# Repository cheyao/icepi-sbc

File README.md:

# Icepi SBC

A low-cost single-board computer for the H3 CPU: A cheap yet powerful Linux device that you can take anywhere.

| Interested? [Subscribe to updates!](https://cyao.dev/subscribe.html) | Check out [Icepi Zero](https://github.com/cheyao/icepi-zero) too |
| -------------------------------------------------------------------- | ---------------------------------------------------------------- |

If there's a lot of people interested, there's a chance that I'll try to sell this at a relatively low price :P

## Features

- H3 Quad-Core ARM Cortex-A7 @ 1.296GHz CPU
    - Mali400 MP2 OpenGL ES 2.0 GPU
- 512MiB of DDR3 RAM, stable at 696MHz (Upgradable to 1GiB)
- Ethernet PHY, WiFi & Bluetooth
- GPDI video out
- USB connectors:
    - 2x USB-A 
    - 2x USB-C (One OTG port)
    - 1x USB-C 100W PD power port
- 3.5mm audio jack
- uSD card slot
- eMMC 5.1 storage

## System support

The single-board computer is capable of running Linux (debian) and Android ([H3Droid](https://h3droid.com/project)). It can output 4k video via it's GPDI-A connector, output a tty consol via UART, or act as an remote host via ssh.

It's small, compact form factor allows it to be a nice portable computer that you can take anywhere! It supports GPU acceleration and 4k video decoding, letting you view anything in full confort.

## PCB

[Check out the online version here](https://github.com/cheyao/icepi-sbc/tree/main/hardware).

The PCB is only 4 layered, ensuring minimal cost and overhead during production. But for mass production 6 layers is recommended, putting solid ground on In.1 and In.4, then copy the power plane to In.2 and In.3. (Impedance matching might be required depending on stackup)

The current setup uses [JLCPCB's](https://jlcpcb.com/) JLC04161H-3313 stackup, and the BOM is optimized for use there. Using other fabs would require re-tuning the DDR3, USB and GPDI traces.

## Open source

This project is licensed under the [Solderpad](/LICENSE) hardware license, granting the maximum amount of liberty :)

It is also OSHWA certified under the identifier [FR000029](https://certification.oshwa.org/fr000029.html).

## Contact

Any questions? Dm `@Cyao.` on Discord (Send a friend request or join the KiCAD Discord server) or send an email to `cyao _at_ duck.com`!

## Bonus

POV: Running Android on the single board computer to study Eigenvectors in the middle of the night:

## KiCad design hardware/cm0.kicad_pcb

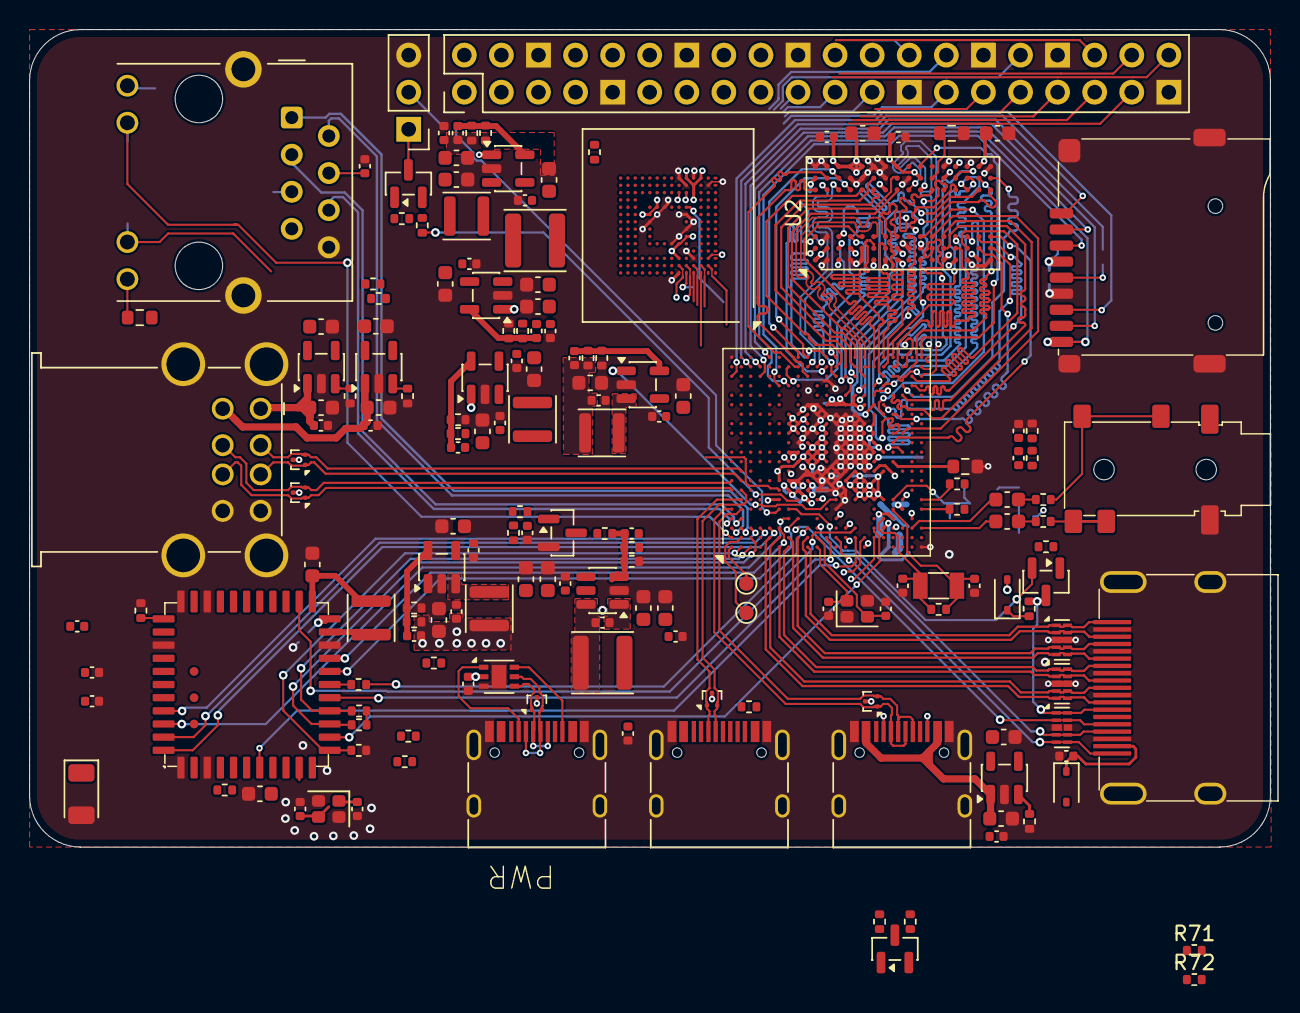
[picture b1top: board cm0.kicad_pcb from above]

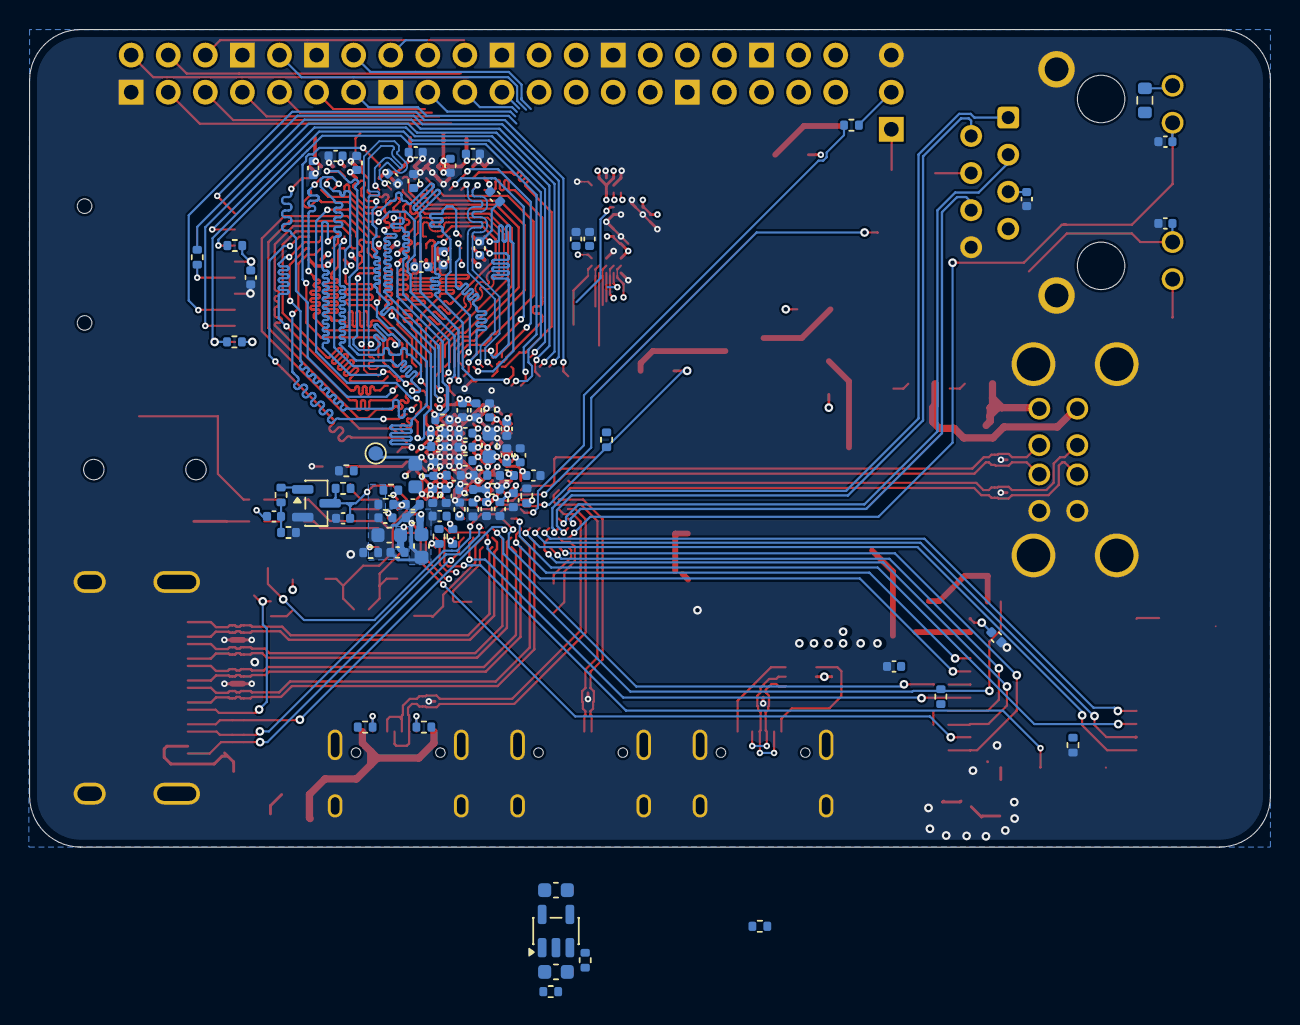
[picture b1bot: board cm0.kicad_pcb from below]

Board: 4 copper layers, 85.0 x 56.0 mm, 253 parts (85 on the bottom side), 209 nets.

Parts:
AE1: 2450AT18A100E; Johanson_2450AT18x100
C1, C2, C3, C4, C7, C8, C12, C14, C18, C19, C23, C24, C26, C27, C29, C31, C37, C38, C40, C41, C42, C43, C46, C47, C48, C49, C52, C53, C54, C55, C56, C57, C58, C60, C62, C65, C67, C70, C72, C76, C78, C81, C84, C85, C90, C92, C95, C98, C101, C104, C108, C110, C113, C114, C121, C122, C123, C124, C130: 100nF; C_0402_1005Metric
C5, C59, C75, C80, C82, C87, C93: 22uF; C_0603_1608Metric
C10, C11, C32, C129: 4.7uF; C_0402_1005Metric
C13, C16, C17, C21, C22, C25, C33, C35, C36, C45, C51, C107, C109, C111: 1uF; C_0402_1005Metric
C15, C20, C28, C30, C44, C50, C63, C64, C68, C69, C73, C79, C83, C86, C89, C96, C97, C99, C100, C102, C103, C105, C106, C112, C118, C125, C126: 10uF; C_0603_1608Metric
C34, C39, C127, C128: 15pF; C_0402_1005Metric
C61, C66, C71, C77, C88, C91: 22pF; C_0402_1005Metric
C94, C116, C117: NC; C_0402_1005Metric
C115, C119, C120: 10pF; C_0402_1005Metric
D1, D2: 1N5819WS; D_SOD-323
J1: USB_A_Stacked; USB_A_SHOUHAN_AF_SS-JB17.6_Horizontal_Stacked
J2, J3, J4: USB_C_Receptacle_USB2.0_14P; USB_C_Receptacle_HRO_TYPE-C-31-M-12
J5: GPDI_A; GPDI_A_XUNPU_001S
J6: Micro_SD_Card_Det1; microSD_TF-01A
J7: RJ45_Hanrun_HR913550A_Horizontal; RJ45_Hanrun_HR911105A_Horizontal
J8: Conn_01x03; PinHeader_1x03_P2.54mm_Vertical
J9: GPIO; PinHeader_2x20_P2.54mm_Vertical
J10: AudioJack_PJ-342; Jack_3.5mm_SHOUHAN_PJ-342
L1, L2, L3, L6, L7: 2.2uH; L_Sunlord_SWPA3015S
L4, L5: 2.2uH; L_Sunlord_SWPA4030S
Q1, Q3, Q4: BSN20; SOT-23
Q2: AO3415A; SOT-23
Q5: MMBT3904; SOT-23
R1: 6.04k; R_0402_1005Metric
R2, R9, R54, R55: 240; R_0603_1608Metric
R3, R5, R24: 0; R_0402_1005Metric
R4: 220k; R_0402_1005Metric
R6: 10M; R_0402_1005Metric
R7, R8, R39, R40, R71, R72: 2k; R_0402_1005Metric
R10, R11, R12, R15, R16, R20, R23, R25, R31, R32, R33, R36, R41, R45, R51, R56, R63, R64, R65: 10k; R_0402_1005Metric
R13, R17, R26: 2.2k; R_0402_1005Metric
R14: 15k; R_0402_1005Metric
R18, R19, R27, R52, R62, R69, R70: 100k; R_0402_1005Metric
R21: 11.8K; R_0402_1005Metric
R22, R28, R37, R38, R46, R47, R48, R49, R50: 33k; R_0402_1005Metric
R29, R30, R34, R35, R42, R43: 56k; R_0402_1005Metric
R44, R53, R57, R58, R59, R60: 33; R_0402_1005Metric
R61, R66, R67, R68: 47k; R_0402_1005Metric
TP1, TP2, TP3: TestPoint; TestPoint_Pad_D1.0mm
U1: H3; FBGA-347_14x14mm_Layout21x21_P0.65mm
U2: H5TQ4G63EFR; FBGA-96_7.5x13mm_Layout9x16_P0.8mm
U3, U4, U5, U8: SY8088; SOT-23-5
U6: SY8089A; SOT-23-5
U7: SY8113; TSOT-23-6
U9, U10, U11, U12: SY6280AAC; SOT-23-5
U13, U14, U15, U16, U18: TPD2EUSB30; Texas_DRT-3
U17: HUSB237; DFN-6-1EP_2x2mm_P0.65mm_EP1x1.6mm
U19, U20, U23: UCL0524P; Diodes_UDFN-10_1.0x2.5mm_P0.5mm
U21: EMMC5.1_BGA153; LFBGA-153_11.5x13mm_Layout14x14_P0.5mm
U22: AP6212
Y1: 32kHz; Crystal_SMD_3215-2Pin_3.2x1.5mm
Y2: 26MHz; Crystal_SMD_2016-4Pin_2.0x1.6mm
Y3: 24MHz; Crystal_SMD_2016-4Pin_2.0x1.6mm

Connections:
+1V1_CPUX: C15.1, C16.2, C17.2, C18.2, C19.2, C85.2, C86.1, C87.1, L5.2, U1.N8 (VDD-CPUX), U1.P6 (VDD-CPUX), U1.P7 (VDD-CPUX), U1.P8 (VDD-CPUX), U1.P9 (VDD-CPUX), U1.R6 (VDD-CPUX), U1.R7 (VDD-CPUX), U1.R8 (VDD-CPUX), U1.T6 (VDD-CPUX), U1.T7 (VDD-CPUX), U1.T8 (VDD-CPUX), U1.U6 (VDD-CPUX), U1.U9 (VDD-CPUX)
+1V2_SYSTEM: C4.2, C20.1, C21.2, C22.2, C23.2, C24.2, C77.1, C78.2, C79.1, C80.1, L4.2, R18.2, U1.F8 (EPHY_VDD), U1.H10 (VDD-SYS), U1.J10 (VDD-SYS), U1.J11 (VDD-SYS), U1.J12 (VDD-SYS), U1.K10 (VDD-SYS), U1.K11 (VDD-SYS), U1.K12 (VDD-SYS), U1.L10 (VDD-SYS), U1.L11 (VDD-SYS), U1.L12 (VDD-SYS), U1.L13 (VDD-SYS), U1.L14 (VDD-SYS)
+1V5: C35.2, C36.2, C37.2, C38.2, C42.1, C44.1, C45.2, C46.1, C47.1, C48.1, C49.1, C50.1, C51.2, C52.1, C53.1, C54.1, C55.1, C56.1, C57.1, C58.1, C66.1, C67.2, C68.1, L2.2, R7.2, R14.2, U1.L16 (VCC-DRAM), U1.M16 (VCC-DRAM), U1.N16 (VCC-DRAM), U1.P16 (VCC-DRAM), U1.P17 (VCC-DRAM), U1.R16 (VCC-DRAM), U1.T12 (VCC-DRAM), U1.T13 (VCC-DRAM), U1.T14 (VCC-DRAM), U1.T15 (VCC-DRAM), U1.U11 (VCC-DRAM), U2.A1 (VDDQ), U2.A8 (VDDQ), U2.B2 (VDD), U2.C1 (VDDQ), U2.C9 (VDDQ), U2.D2 (VDDQ), U2.D9 (VDD), U2.E9 (VDDQ), U2.F1 (VDDQ), U2.G7 (VDD), U2.H2 (VDDQ), U2.H9 (VDDQ), U2.K2 (VDD), U2.K8 (VDD), U2.N1 (VDD), U2.N9 (VDD), U2.R1 (VDD), U2.R9 (VDD)
+3V3: R41.1, U21.C6 (VCCQ), U21.E6 (VCC), U21.F5 (VCC), U21.J10 (VCC), U21.K9 (VCC), U21.M4 (VCCQ), U21.N4 (VCCQ), U21.P3 (VCCQ), U21.P5 (VCCQ)
+3V3_AVCC: C5.1, C7.2, C12.2, C27.2, C28.1, C29.2, C71.1, C72.2, C73.1, L3.2, Q2.2 (S), R10.1, R11.1, R15.2, R23.1, R61.1, R62.1, R65.1, R66.1, R68.1, U1.G9 (V33_TV), U1.K6 (VCC_RTC), U1.N3 (VCC_PLL), U1.V3 (AVCC)
+3V3_IO: C1.2, C2.2, C3.2, C8.2, C13.2, C14.2, C91.1, C92.2, C93.1, C109.2, C129.1, D1.2 (A), J6.4 (VDD), J9.1, L6.2, Q3.1 (G), Q4.1 (G), R25.2, R37.1, R42.1, R43.1, R54.1, R55.1, R56.1, R67.1, U1.G7 (EPHY_VCC), U1.G11 (VCC_USB), U1.G13 (VCC-IO), U1.G14 (VCC-IO), U1.G15 (VCC-IO), U1.H7 (VCC-PG), U1.H11 (VDD-EFUSEEBP), U1.H13 (VCC-IO), U1.H14 (VCC-IO), U1.J6 (GPDI_VCC), U1.J14 (VCC-IO), U1.J15 (VCC_PD)
+3V3_WIFI: C61.1, C62.2, C63.1, C112.1, C113.1, C114.1, L1.2, R12.2, R45.1, R46.1, R47.1, R48.1, R49.1, R50.1, R51.1, U22.9 (VBAT), U22.22 (VDDIO)
+5V: C59.1, C60.2, C64.1, C65.2, C69.1, C70.2, C75.1, C76.2, C82.1, C83.1, C84.2, C89.1, C90.2, C97.1, C100.1, C103.1, C106.1, C107.2, D2.2 (A), J4.A4 (VBUS), J4.A9 (VBUS), J4.B4 (VBUS), J4.B9 (VBUS), J9.2, J9.4, R39.2, R40.2, U3.1 (EN), U3.4 (IN), U4.4 (IN), U5.1 (EN), U5.4 (IN), U6.4 (IN), U7.5 (IN), U8.4 (IN), U9.4 (EN), U9.5 (IN), U10.4 (EN), U10.5 (IN), U11.4 (EN), U11.5 (IN), U12.4 (EN), U12.5 (IN), U17.2 (VBUS)
/Audio/AUDIO_L: C126.2, U1.AA3 (LINEOUTL)
/Audio/AUDIO_R: C125.2, U1.Y3 (LINEOUTR)
/Audio/TV_OUT: J10.1, U1.F10 (TVOUT)
/DDR3/A0: U1.T17 (SA0), U2.N3 (A0)
/DDR3/A1: U1.U18 (SA1), U2.P7 (A1)
/DDR3/A2: U1.V19 (SA2), U2.P3 (A2)
/DDR3/A3: U1.V20 (SA3), U2.N2 (A3)
/DDR3/A4: U1.V21 (SA4), U2.P8 (A4)
/DDR3/A5: U1.Y19 (SA5), U2.P2 (A5)
/DDR3/A6: U1.Y20 (SA6), U2.R8 (A6)
/DDR3/A7: U1.V15 (SA7), U2.R2 (A7)
/DDR3/A8: U1.W18 (SA8), U2.T8 (A8)
/DDR3/A9: U1.Y18 (SA9), U2.R3 (A9)
/DDR3/A10: U1.P19 (SA10), U2.L7 (A10/AP)
/DDR3/A11: U1.N19 (SA11), U2.R7 (A11)
/DDR3/A12: U1.R18 (SA12), U2.N7 (A12/~BC)
/DDR3/A13: U1.V12 (SA13), U2.T3 (A13)
/DDR3/A14: U1.N17 (SA14), U2.T7 (A14)
/DDR3/A15: U1.R17 (SA15), U2.M7 (A15)
/DDR3/BA0: U1.W17 (SBA0), U2.M2 (BA0)
/DDR3/BA1: U1.T18 (SBA1), U2.N8 (BA1)
/DDR3/BA2: U1.V17 (SBA2), U2.M3 (BA2)
/DDR3/CKE: U1.AA21 (SCKE0), U2.K9 (CKE)
/DDR3/CLK+: U1.AA19 (SCK), U2.J7 (CK)
/DDR3/CLK-: U1.AA20 (SCKB), U2.K7 (~CK)
/DDR3/DQ0: U1.T20 (SDQ5), U2.E3 (DQ0)
/DDR3/DQ1: U1.P20 (SDQ2), U2.F7 (DQ1)
/DDR3/DQ2: U1.U19 (SDQ6), U2.F2 (DQ2)
/DDR3/DQ3: U1.N20 (SDQ0), U2.F8 (DQ3)
/DDR3/DQ4: U1.U20 (SDQ7), U2.H3 (DQ4)
/DDR3/DQ5: U1.P21 (SDQ1), U2.H8 (DQ5)
/DDR3/DQ6: U1.U21 (SDQ3), U2.G2 (DQ6)
/DDR3/DQ7: U1.R19 (SDQ4), U2.H7 (DQ7)
/DDR3/DQ8: U1.J21 (SDQ11), U2.D7 (DQ8)
/DDR3/DQ9: U1.M21 (SDQ14), U2.C3 (DQ9)
/DDR3/DQ10: U1.H21 (SDQ10), U2.C8 (DQ10)
/DDR3/DQ11: U1.M19 (SDQ15), U2.C2 (DQ11)
/DDR3/DQ12: U1.J19 (SDQ8), U2.A7 (DQ12)
/DDR3/DQ13: U1.L21 (SDQ13), U2.A2 (DQ13)
/DDR3/DQ14: U1.H20 (SDQ9), U2.B8 (DQ14)
/DDR3/DQ15: U1.L20 (SDQ12), U2.A3 (DQ15)
/DDR3/DQM0: U1.M20 (SDQM0), U2.E7 (LDM)
/DDR3/DQM1: U1.G20 (SDQM1), U2.D3 (UDM)
/DDR3/DQS0+: U1.R20 (SDQS0), U2.F3 (LDQS)
/DDR3/DQS0-: U1.R21 (SDQS0B), U2.G3 (~LDQS)
/DDR3/DQS1+: U1.K20 (SDQS1), U2.C7 (UDQS)
/DDR3/DQS1-: U1.J20 (SDQS1B), U2.B7 (~UDQS)
/DDR3/ODT: U1.W11 (SODT0), U2.K1 (ODT)
/DDR3/~CAS: U1.U15 (SCAS), U2.K3 (~CAS)
/DDR3/~CS: U1.W20 (SCS0), U2.L2 (~CS)
/DDR3/~RAS: U1.V13 (SRAS), U2.J3 (~RAS)
/DDR3/~RESET: U1.U16 (SRST), U2.T2 (~RESET)
/DDR3/~WE: U1.W13 (SWE), U2.L3 (~WE)
/GPDI/GPDI_CEC: Q3.2 (S), R37.2, U1.G5 (GPDI_CEC)
/GPDI/GPDI_CECI: J5.13 (CEC), Q3.3 (D), R38.2, U23.1, U23.10
/GPDI/GPDI_CLK+: J5.10 (CK+), U1.F2 (GPDI_CLK+), U20.4, U20.7
/GPDI/GPDI_CLK-: J5.12 (CK-), U1.E2 (GPDI_CLK-), U20.5, U20.6
/GPDI/GPDI_D0+: J5.7 (D0+), U1.G1 (GPDI_D0+), U20.1, U20.10
/GPDI/GPDI_D0-: J5.9 (D0-), U1.F1 (GPDI_D0-), U20.2, U20.9
/GPDI/GPDI_D1+: J5.4 (D1+), U1.H2 (GPDI_D1+), U19.4, U19.7
/GPDI/GPDI_D1-: J5.6 (D1-), U1.G2 (GPDI_D1-), U19.5, U19.6
/GPDI/GPDI_D2+: J5.1 (D2+), U1.J1 (GPDI_D2+), U19.1, U19.10
/GPDI/GPDI_D2-: J5.3 (D2-), U1.J2 (GPDI_D2-), U19.2, U19.9
/GPDI/GPDI_HPD: J5.19 (HPD), U1.M2 (GPDI_HPD), U23.5, U23.6
/GPDI/GPDI_SCL: J5.15 (SCL), R40.1, U1.H3 (GPDI_SCL), U23.2, U23.9
/GPDI/GPDI_SDA: J5.16 (SDA), R39.1, U1.K3 (GPDI_SDA), U23.4, U23.7
/GPIO/CPU_RX: R57.1, U1.H6 (PA5)
/GPIO/CPU_TX: R58.1, U1.F5 (PA4)
/H3/AGND: C28.2, C29.1, C30.2, C31.1, C32.2, C33.1, R4.2, R5.1, U1.U3 (AGND)
/H3/BT_HOST_WAKE: U1.P2 (PL2), U22.7 (BT_HOST_WAKE)
/H3/BT_RXD: U1.D3 (UART1_RX), U22.43 (UART_RXD)
/H3/BT_TXD: U1.G4 (UART1_TX), U22.42 (UART_TXD)
/H3/BT_WAKE: R45.2, R69.1, U1.A13 (PA20), U22.6 (BT_WAKE)
/H3/EPHY_LINK_LED: C124.1, J7.10, U1.A2 (EPHY_LINK_LED)
/H3/EPHY_RX+: J7.3 (RD+), U1.B4 (EPHY_RXP)
/H3/EPHY_RX-: J7.6 (RD-), U1.A4 (EPHY_RXN)
/H3/EPHY_SPD_LED: C123.1, J7.11, U1.F7 (EPHY_SPD_LED)
/H3/EPHY_TX+: J7.1 (TD+), U1.B3 (EPHY_TXP)
/H3/EPHY_TX-: J7.2 (TD-), U1.A3 (EPHY_TXN)
/H3/KEYADC: R62.2, U1.AA5 (KEYADC)
/H3/PWR_CPUFB: C88.1, R20.1, TP1.1, U1.T10 (VDD-CPUFB)
/H3/PWR_DRAM: R10.2, U1.M6 (PL9), U4.1 (EN)
/H3/PWR_IO: Q2.1 (G), R27.2, U1.R2 (PL5)
/H3/PWR_KEY: R66.2, U1.R1 (PL3)
/H3/PWR_SYSTEM: R11.2, U1.T2 (PL8), U6.1 (EN), U7.4 (EN)
/H3/PWR_VSET: R24.2, U1.T4 (PL6)
/H3/RECOVERY: R68.2, U1.N2 (PL4)
/H3/RESET: C130.2, Q5.3 (C), R65.2, U1.V6 (RESET)
/H3/SDIO_CLK: R53.1, U1.J3 (SDC1_CLK)
/H3/SDIO_CMD: R50.2, U1.L2 (SDC1_CMD), U22.16 (SDIO_DATA_CMD)
/H3/SDIO_D0: R49.2, U1.H4 (SDC1_D0), U22.18 (SDIO_DATA_0)
/H3/SDIO_D1: R48.2, U1.F3 (SDC1_D1), U22.19 (SDIO_DATA_1)
/H3/SDIO_D2: R47.2, U1.C2 (SDC1_D2), U22.14 (SDIO_DATA_2)
/H3/SDIO_D3: R46.2, U1.C1 (SDC1_D3), U22.15 (SDIO_DATA_3)
/H3/SD_CLK: R44.1, U1.D20 (PF2)
/H3/SD_CMD: J6.3 (CMD), R42.2, U1.F18 (PF3)
/H3/SD_D0: J6.7 (DAT0), U1.A19 (PF1)
/H3/SD_D1: J6.8 (DAT1), U1.D19 (PF0)
/H3/SD_D2: J6.1 (DAT2), U1.C20 (PF5)
/H3/SD_D3: J6.2 (DAT3/CD), U1.E21 (PF4)
/H3/SD_DET: J6.9 (DET), R43.2, U1.G18 (PF6)
/H3/UBOOT: R67.2, U1.W6 (UBOOT)
/H3/USB_D0+: J2.A7 (D-), J2.B7 (D-), U1.A5 (USB_D0+), U13.1 (D+)
/H3/USB_D0-: J2.A6 (D+), J2.B6 (D+), U1.B5 (USB_D0-), U13.2 (D-)
/H3/USB_D1+: J3.A7 (D-), J3.B7 (D-), U1.B6 (USB_D1+), U15.1 (D+)
/H3/USB_D1-: J3.A6 (D+), J3.B6 (D+), U1.B7 (USB_D1-), U15.2 (D-)
/H3/USB_D2+: J1.7 (D2+), U1.A7 (USB_D2+), U14.1 (D+)
/H3/USB_D2-: J1.6 (D2-), U1.A8 (USB_D2-), U14.2 (D-)
/H3/USB_D3+: J1.3 (D1+), U1.B8 (USB_D3+), U16.1 (D+)
/H3/USB_D3-: J1.2 (D1-), U1.B9 (USB_D3-), U16.2 (D-)
/H3/VRA1: C33.2, U1.Y4 (VRA1)
/H3/VRA2: C32.1, R4.1, U1.W5 (VRA2)
/H3/VRP: C30.1, C31.2, U1.V4 (VRP)
/H3/WIFI_32K: R51.2, U1.P3 (X32KFOUT), U22.24 (LPO)
/H3/WL_HOST_WAKE: U1.T3 (PL7), U22.13 (WL_HOST_WAKE)
/H3/WL_REG_ON: R52.1, U1.B1 (PG13), U22.12 (WL_REG_ON)
/H3/X24MI: C127.1, U1.K2 (X24MIN), Y3.2
/H3/X24MO: C128.1, U1.K1 (X24MOUT), Y3.4
/H3/X32KI: C34.1, R6.1, U1.V5 (X32KIN), Y1.2
/H3/X32KO: C39.1, R6.2, U1.U4 (X32KOUT), Y1.1
/H3/eMMC_CLK: U1.A17 (PC5), U21.M6 (CLK)
/H3/eMMC_CMD: R41.2, U1.E16 (PC6), U21.M5 (CMD)
/H3/eMMC_D0: U1.B18 (PC8), U21.A3 (DAT0)
/H3/eMMC_D1: U1.C17 (PC9), U21.A4 (DAT1)
/H3/eMMC_D2: U1.D17 (PC10), U21.A5 (DAT2)
/H3/eMMC_D3: U1.C18 (PC11), U21.B2 (DAT3)
/H3/eMMC_D4: U1.B17 (PC12), U21.B3 (DAT4)
/H3/eMMC_D5: U1.B19 (PC13), U21.B4 (DAT5)
/H3/eMMC_D6: U1.F17 (PC14), U21.B5 (DAT6)
/H3/eMMC_D7: U1.C19 (PC15), U21.B6 (DAT7)
/H3/~BT_CTS: U1.E3 (UART1_CTS), U22.44 (UART_CTS_N)
/H3/~BT_RST: R70.1, U1.D13 (PA9), U22.34 (BT_RST_N)
/H3/~BT_RTS: U1.C3 (UART1_RTS), U22.41 (UART_RTS_N)
/H3/~eMMC_RST: U1.H16 (PC16), U21.K5 (~RST)
/USB/PWR_CC1: J4.A5 (CC1), U17.1 (CC1)
/USB/PWR_CC2: J4.B5 (CC2), U17.6 (CC2)
/USB/PWR_D+: J4.A6 (D+), J4.B6 (D+), U17.4 (D+), U18.1 (D+)
/USB/PWR_D-: J4.A7 (D-), J4.B7 (D-), U17.5 (D-), U18.2 (D-)
/USB/USB_VBUS0: C95.2, C96.1, J2.A4 (VBUS), J2.A9 (VBUS), J2.B4 (VBUS), J2.B9 (VBUS), R29.1, R30.1, U9.1 (OUT)
/USB/USB_VBUS1: C104.2, C105.1, J3.A4 (VBUS), J3.A9 (VBUS), J3.B4 (VBUS), J3.B9 (VBUS), R34.1, R35.1, U12.1 (OUT)
/USB/USB_VBUS2: C98.2, C99.1, J1.1 (VBUS1), U10.1 (OUT)
/USB/USB_VBUS3: C101.2, C102.1, J1.5 (VBUS2), U11.1 (OUT)
GND: AE1.2 (Shield), C1.1, C2.1, C3.1, C4.1, C5.2, C7.1, C8.1, C10.2, C11.2, C12.1, C13.1, C14.1, C15.2, C16.1, C17.1, C18.1, C19.1, C20.2, C21.1, C22.1, C23.1, C24.1, C25.1, C26.1, C27.1, C34.2, C35.1, C36.1, C37.1, C38.1, C39.2, C40.2, C41.2, C43.2, C44.2, C45.1, C46.2, C47.2, C48.2, C49.2, C50.2, C51.1, C52.2, C53.2, C54.2, C55.2, C56.2, C57.2, C58.2, C59.2, C60.1, C62.1, C63.2, C64.2, C65.1, C67.1, C68.2, C69.2, C70.1, C72.1, C73.2, C75.2, C76.1, C78.1, C79.2, C80.2, C82.2, C83.2, C84.1, C85.1, C86.2, C87.2, C89.2, C90.1, C92.1, C93.2, C94.2, C95.1, C96.2, C97.2, C98.1, C99.2, C100.2, C101.1, C102.2, C103.2, C104.1, C105.2, C106.2, C107.1, C108.1, C109.1, C110.2, C111.1, C112.2, C113.2, C114.2, C116.2, C117.2, C118.2, C119.2, C120.2, C121.1, C122.1, C123.2, C124.2, C127.2, C128.2, C130.1, J1.4 (GND1), J1.8 (GND2), J1.9 (Shield), J2.A1 (GND), J2.A12 (GND), J2.B1 (GND), J2.B12 (GND), J2.S1 (SHIELD), J3.A1 (GND), J3.A12 (GND), J3.B1 (GND), J3.B12 (GND), J3.S1 (SHIELD), J4.A1 (GND), J4.A12 (GND), J4.B1 (GND), J4.B12 (GND), J4.S1 (SHIELD), J5.2 (D2S), J5.5 (D1S), J5.8 (D0S), J5.11 (CKS), J5.17 (GND), J5.SH, J6.6 (VSS), J6.10 (SHIELD), J7.8, J7.SH, J8.3, J9.6, J9.9, J9.14, J9.20, J9.25, J9.30, J9.34, J9.39, J10.2, Q1.2 (S), Q5.2 (E), R1.2, R2.1, R3.2, R5.2, R8.1, R9.2, R13.1, R16.1, R17.1, R19.1, R21.2, R26.1, R27.1, R28.2, R31.2, R32.2, R33.2, R36.2, R52.2, R63.2, R69.2, R70.2, U1.A21 (GND), U1.AA1 (GND), U1.G8 (GND), U1.H8 (GND_TV), U1.H12 (GND), U1.H15 (GND), U1.J9 (GND), U1.J13 (GND), U1.J16 (GND), U1.K7 (GND), U1.K8 (GND), U1.K9 (GND), U1.K13 (GND), U1.K14 (GND), U1.K15 (GND), U1.K16 (GND), U1.L8 (GND), U1.L9 (GND), U1.L15 (GND), U1.M5 (GPDI_GND), U1.M7 (GND), U1.M8 (GND), U1.M9 (GND), U1.M10 (GND), U1.M11 (GND), U1.M12 (GND), U1.M13 (GND), U1.M14 (GND), U1.M15 (GND), U1.N7 (GND), U1.N9 (GND), U1.N10 (GND), U1.N11 (GND), U1.N12 (GND), U1.N13 (GND), U1.N14 (GND), U1.N15 (GND), U1.P10 (GND), U1.P11 (GND), U1.P12 (GND), U1.P13 (GND), U1.P14 (GND), U1.P15 (GND), U1.R9 (GND), U1.R10 (GND), U1.R11 (GND), U1.R12 (GND), U1.R13 (GND), U1.R14 (GND), U1.T11 (GND), U2.A9 (VSS), U2.B1 (VSSQ), U2.B3 (VSS), U2.B9 (VSSQ), U2.D1 (VSSQ), U2.D8 (VSSQ), U2.E1 (VSS), U2.E2 (VSSQ), U2.E8 (VSSQ), U2.F9 (VSSQ), U2.G1 (VSSQ), U2.G8 (VSS), U2.G9 (VSSQ), U2.J2 (VSS), U2.J8 (VSS), U2.M1 (VSS), U2.M9 (VSS), U2.P1 (VSS), U2.P9 (VSS), U2.T1 (VSS), U2.T9 (VSS), U3.2 (GND), U4.2 (GND), U5.2 (GND), U6.2 (GND), U7.2 (GND), U8.2 (GND), U9.2 (GND), U10.2 (GND), U11.2 (GND), U12.2 (GND), U13.3 (GND), U14.3 (GND), U15.3 (GND), U16.3 (GND), U17.3 (VSET), U17.7 (GND), U18.3 (GND), U19.3, U19.8, U20.3, U20.8, U21.A6 (VSS), U21.C4 (VSSQ), U21.E7 (VSS), U21.G5 (VSS), U21.H10 (VSS), U21.J5 (VSS), U21.K8 (VSSQ), U21.N2 (VSSQ), U21.N5 (VSSQ), U21.P4 (VSSQ), U21.P6 (VSSQ), U22.1 (GND), U22.3 (GND), U22.20 (GND), U22.31 (GND), U22.33 (GND), U22.36 (GND), U23.3, U23.8, Y2.2, Y2.4, Y3.1, Y3.3
unnamed: AE1.1 (A), C115.2, C116.1, C117.1
unnamed: C125.1, R59.2
unnamed: C126.1, R60.2
unnamed: C129.2, R63.1, R64.1
unnamed: D1.1 (K), R38.1
unnamed: C108.2, D2.1 (K), J5.18 (+5V)
unnamed: J2.A5 (CC1), R29.2
unnamed: J2.B5 (CC2), R30.2
unnamed: J3.A5 (CC1), R34.2
unnamed: J3.B5 (CC2), R35.2
unnamed: J6.5 (CLK), R44.2
unnamed: J7.9, R55.2
unnamed: J7.12, R54.2
unnamed: C122.2, J7.5 (RCT)
unnamed: C121.2, J7.4 (TCT)
unnamed: J8.1, Q4.3 (D)
unnamed: J8.2, R58.2
unnamed: J10.3, J10.5, R59.1
unnamed: J10.4, J10.6, R60.1
unnamed: Q1.3 (D), R22.2
unnamed: C94.1, Q1.1 (G), R23.2, R24.1
unnamed: Q2.3 (D), R28.1, U8.1 (EN)
unnamed: Q4.2 (S), R56.2, R57.2
unnamed: Q5.1 (B), R64.2
unnamed: R2.2, U1.V10 (SZQ)
unnamed: C10.1, U1.G10 (VDD-EFUSE)
unnamed: R1.1, U1.F6 (EPHY_RTX)
unnamed: R3.1, U1.T9 (GND-CPUFB)
unnamed: TP2.1, U1.A1 (JTAG-SEL0)
unnamed: TP3.1, U1.B2 (JTAG-SEL1)
unnamed: R61.2, U1.AA6 (NMI)
unnamed: R9.1, U2.L8 (ZQ)
unnamed: C61.2, R12.1, R13.2, U3.5 (FB)
unnamed: L1.1, U3.3 (LX)
unnamed: C66.2, R14.1, R16.2, U4.5 (FB)
unnamed: L2.1, U4.3 (LX)
unnamed: C71.2, R15.1, R17.2, U5.5 (FB)
unnamed: L3.1, U5.3 (LX)
unnamed: C77.2, R18.1, R19.2, U6.5 (FB)
unnamed: L4.1, U6.3 (LX)
unnamed: C81.2, U7.1 (BS)
unnamed: C88.2, R20.2, R21.1, R22.1, U7.3 (FB)
unnamed: C81.1, L5.1, U7.6 (LX)
unnamed: C91.2, R25.1, R26.2, U8.5 (FB)
unnamed: L6.1, U8.3 (LX)
unnamed: R31.1, U9.3 (ISET)
unnamed: R32.1, U10.3 (ISET)
unnamed: R33.1, U11.3 (ISET)
unnamed: R36.1, U12.3 (ISET)
unnamed: C110.1, C111.2, U21.C2 (VDDI)
unnamed: R53.2, U22.17 (SDIO_DATA_CLK)
unnamed: C118.1, L7.2, U22.23 (VIN_LDO)
unnamed: L7.1, U22.21 (VIN_LDO_OUT)
unnamed: C115.1, U22.2 (WL_BT_ANT)
unnamed: C120.1, U22.10 (XTAL_IN), Y2.3
unnamed: C119.1, U22.11 (XTAL_OUT), Y2.1
VDD_CPUS: C11.1, C25.2, C26.2, U1.J7 (VDD-CPUS), U1.J8 (VDD-CPUS), U1.M4 (RTC_VIO)
VREF: C40.1, C41.1, C42.2, C43.1, R7.1, R8.2, U1.T16 (SVREF), U2.H1 (VREFDQ), U2.M8 (VREFCA)

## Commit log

2025-10-31 Routed DDR3
2025-11-02 Drew wifi, GPDI, and re-routed DDR3
2025-11-05 Added TVS diodes, RF switch and changed RJ45 conn
2025-11-09 Drew most of DC DC converters
2025-11-12 Laid out the DCDC bucks
2025-11-13 Even more routing
2025-11-14 Less than 100 traces left
2025-11-15 Add some vital info!
2025-11-18 Improve routing and add test pads
2025-11-19 Production ready
2025-11-24 Improve heat dissipation and layout
2025-12-05 Add some more decoupling and move trace
2025-12-07 Add link
2025-12-24 Bonus pic :-P
2025-12-28 Fix typo in README for Android section
2026-01-09 Pretty up schematic
2026-01-22 Fix broken CDN links
